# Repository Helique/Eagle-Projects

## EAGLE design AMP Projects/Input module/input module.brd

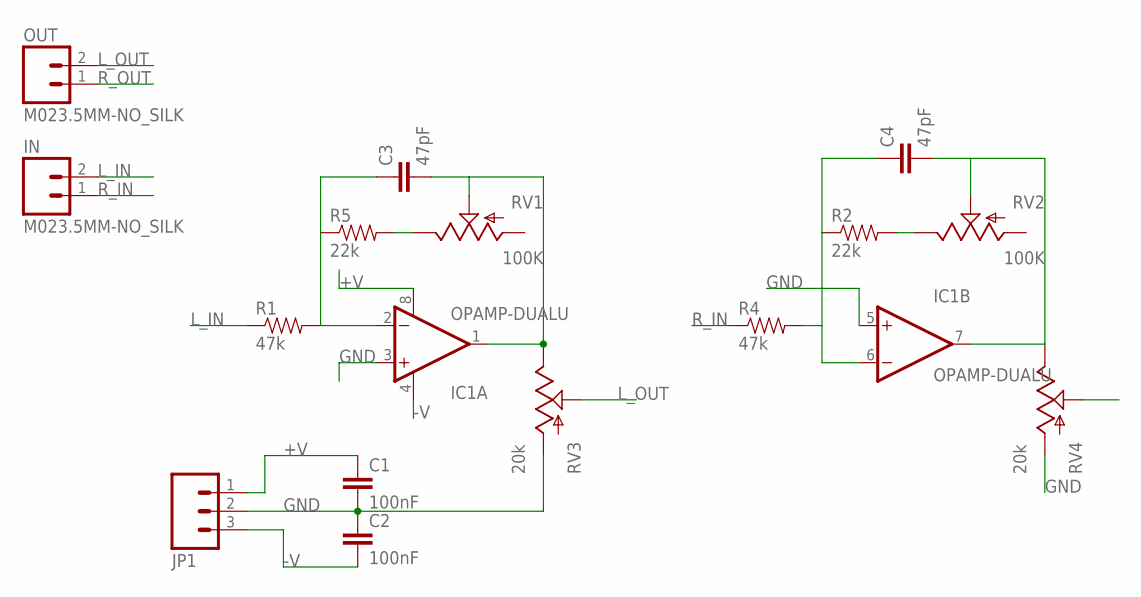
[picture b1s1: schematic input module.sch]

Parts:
C1, C2: 100nF; 1206
C3, C4: 47pF; 0805
IC1: OPAMP-DUALU; SO08
IN: M023.5MM-NO_SILK; SCREWTERMINAL-3.5MM-2-NS
JP1: M03SCREW; SCREWTERMINAL-3.5MM-3
OUT: M023.5MM-NO_SILK; SCREWTERMINAL-3.5MM-2-NS
R1, R4: 47k; AXIAL-0.4
R2, R5: 22k; AXIAL-0.4
RV1, RV2: 100K; TRIM_POT
RV3, RV4: 20k; ALPS_POT

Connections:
+V: C1.1, IC1.8 (V+), JP1.1
-V: C2.2, IC1.4 (V-), JP1.3
GND: C1.2, C2.1, IC1.3 (+IN), IC1.5 (+IN), JP1.2, RV3.P$3 (A), RV4.P$3 (A)
L_IN: IN.2, R1.P$1 (1)
L_OUT: OUT.2, RV3.P$2 (S)
unnamed: R5.P$2 (2), RV1.2 (E)
unnamed: C3.1, IC1.2 (-IN), R1.P$2 (2), R5.P$1 (1)
unnamed: C4.1, IC1.6 (-IN), R2.P$1 (1), R4.P$2 (2)
unnamed: R2.P$2 (2), RV2.2 (E)
unnamed: C4.2, IC1.7 (OUT), RV2.1 (S), RV4.P$1 (E)
unnamed: C3.2, IC1.1 (OUT), RV1.1 (S), RV3.P$1 (E)
R_IN: IN.1, R4.P$1 (1)
R_OUT: OUT.1, RV4.P$2 (S)

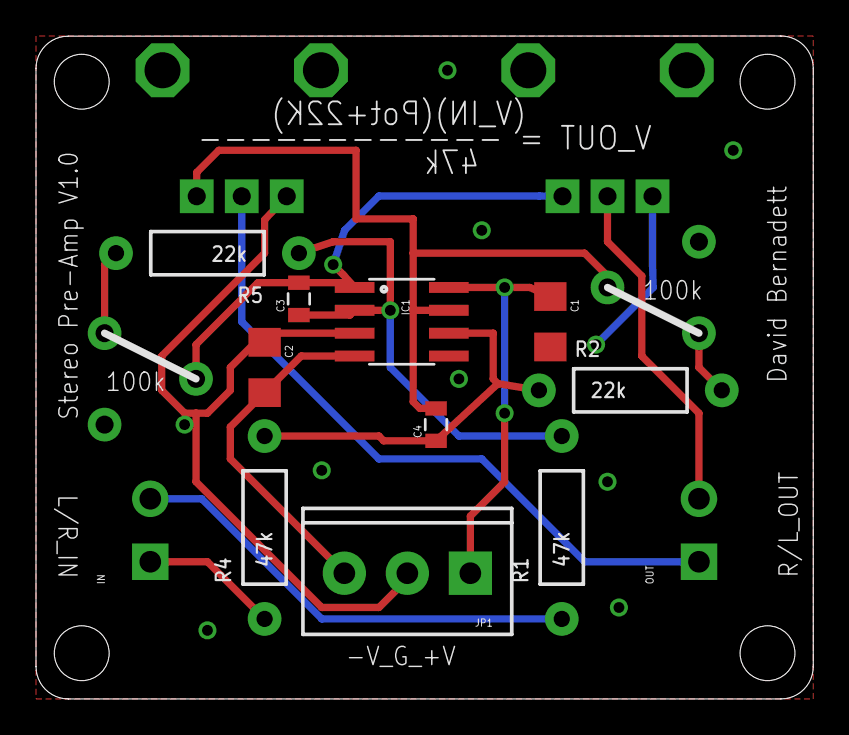
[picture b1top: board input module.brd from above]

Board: 2 copper layers, 43.2 x 36.8 mm, 20 parts (0 on the bottom side), 13 nets.

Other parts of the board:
U$1, U$2, U$3, U$4: STAND-OFF-TIGHT

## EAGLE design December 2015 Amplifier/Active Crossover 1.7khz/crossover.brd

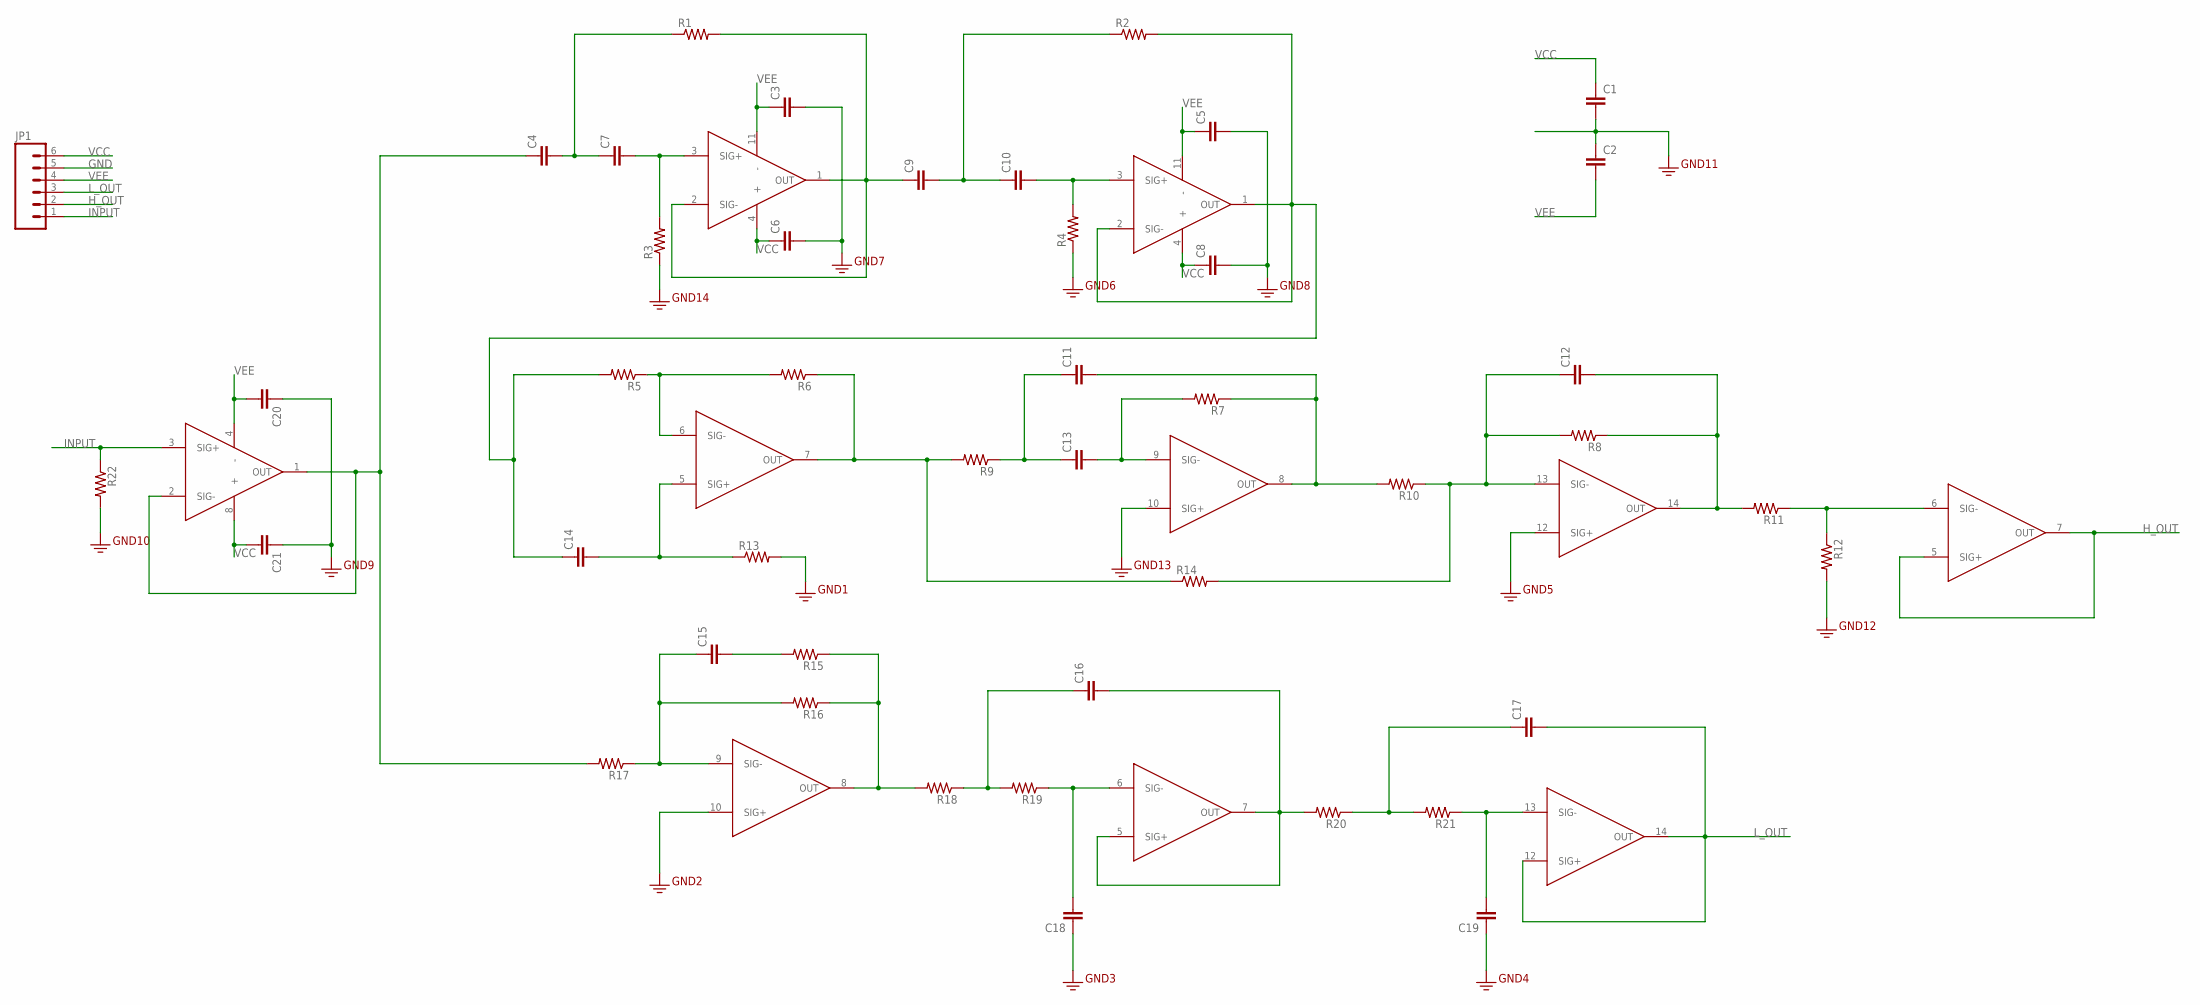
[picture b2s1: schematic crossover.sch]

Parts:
C1, C2, C3, C4, C5, C6, C7, C8, C9, C10, C11, C12, C13, C14, C15, C16, C17, C18, C19, C20, C21: CAPEZ; CAP-PTH-SMALLEZ
JP1: M06SIP; 1X06
R1, R2, R3, R4, R5, R6, R7, R8, R9, R10, R11, R12, R13, R14, R15, R16, R17, R18, R19, R20, R21, R22: RESISTORPTH-1/4W; AXIAL-0.4
U$1, U$2: OPA1604STANDARD; SOIC-14
U$3: OPA1602; SOIC8

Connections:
GND: C1.2, C2.1, C3.2, C5.2, C6.2, C8.2, C18.1, C19.1, C20.1, C21.1, JP1.5, R3.P$1 (1), R4.P$1 (1), R12.P$2 (2), R13.P$2 (2), R22.P$2 (2), U$1.10 (SIG+), U$2.10 (SIG+), U$2.12 (SIG+)
H_OUT: JP1.2, U$3.5 (SIG+), U$3.7 (OUT)
INPUT: JP1.1, R22.P$1 (1), U$3.3 (SIG+)
L_OUT: C17.2, JP1.3, U$1.12 (SIG+), U$1.14 (OUT)
unnamed: C7.2, R3.P$2 (2), U$1.3 (SIG+)
unnamed: C9.1, R1.P$2 (2), U$1.1 (OUT), U$1.2 (SIG-)
unnamed: C4.2, C7.1, R1.P$1 (1)
unnamed: C9.2, C10.1, R2.P$1 (1)
unnamed: C10.2, R4.P$2 (2), U$2.3 (SIG+)
unnamed: C11.2, R7.P$1 (1), R10.P$2 (2), U$2.8 (OUT)
unnamed: C13.2, R7.P$2 (2), U$2.9 (SIG-)
unnamed: C11.1, C13.1, R9.P$1 (1)
unnamed: R6.P$1 (1), R9.P$2 (2), R14.P$1 (1), U$2.7 (OUT)
unnamed: C14.2, R13.P$1 (1), U$2.5 (SIG+)
unnamed: C14.1, R2.P$2 (2), R5.P$2 (2), U$2.1 (OUT), U$2.2 (SIG-)
unnamed: R5.P$1 (1), R6.P$2 (2), U$2.6 (SIG-)
unnamed: C12.1, R8.P$2 (2), R10.P$1 (1), R14.P$2 (2), U$2.13 (SIG-)
unnamed: C12.2, R8.P$1 (1), R11.P$2 (2), U$2.14 (OUT)
unnamed: R11.P$1 (1), R12.P$1 (1), U$3.6 (SIG-)
unnamed: C15.1, R16.P$2 (2), R17.P$1 (1), U$1.9 (SIG-)
unnamed: C15.2, R15.P$2 (2)
unnamed: R15.P$1 (1), R16.P$1 (1), R18.P$2 (2), U$1.8 (OUT)
unnamed: C16.1, R18.P$1 (1), R19.P$2 (2)
unnamed: C18.2, R19.P$1 (1), U$1.6 (SIG-)
unnamed: C16.2, R20.P$2 (2), U$1.5 (SIG+), U$1.7 (OUT)
unnamed: C17.1, R20.P$1 (1), R21.P$2 (2)
unnamed: C19.2, R21.P$1 (1), U$1.13 (SIG-)
unnamed: C4.1, R17.P$2 (2), U$3.1 (OUT), U$3.2 (SIG-)
VCC: C1.1, C6.1, C8.1, C21.2, JP1.6, U$1.4 (+), U$2.4 (+), U$3.8 (+)
VEE: C2.2, C3.1, C5.1, C20.2, JP1.4, U$1.11 (-), U$2.11 (-), U$3.4 (-)

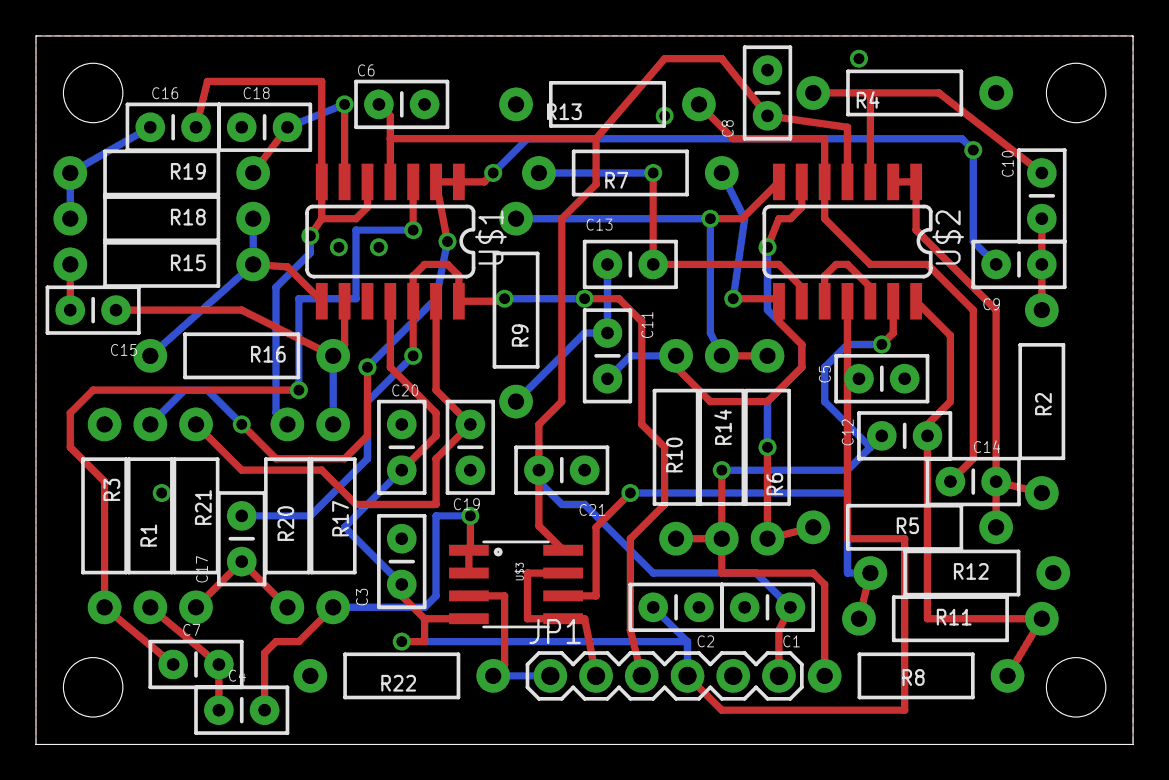
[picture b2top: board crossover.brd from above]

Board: 2 copper layers, 60.9 x 39.4 mm, 51 parts (0 on the bottom side), 30 nets.

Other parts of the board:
U$4, U$5, U$6, U$7: STAND-OFF

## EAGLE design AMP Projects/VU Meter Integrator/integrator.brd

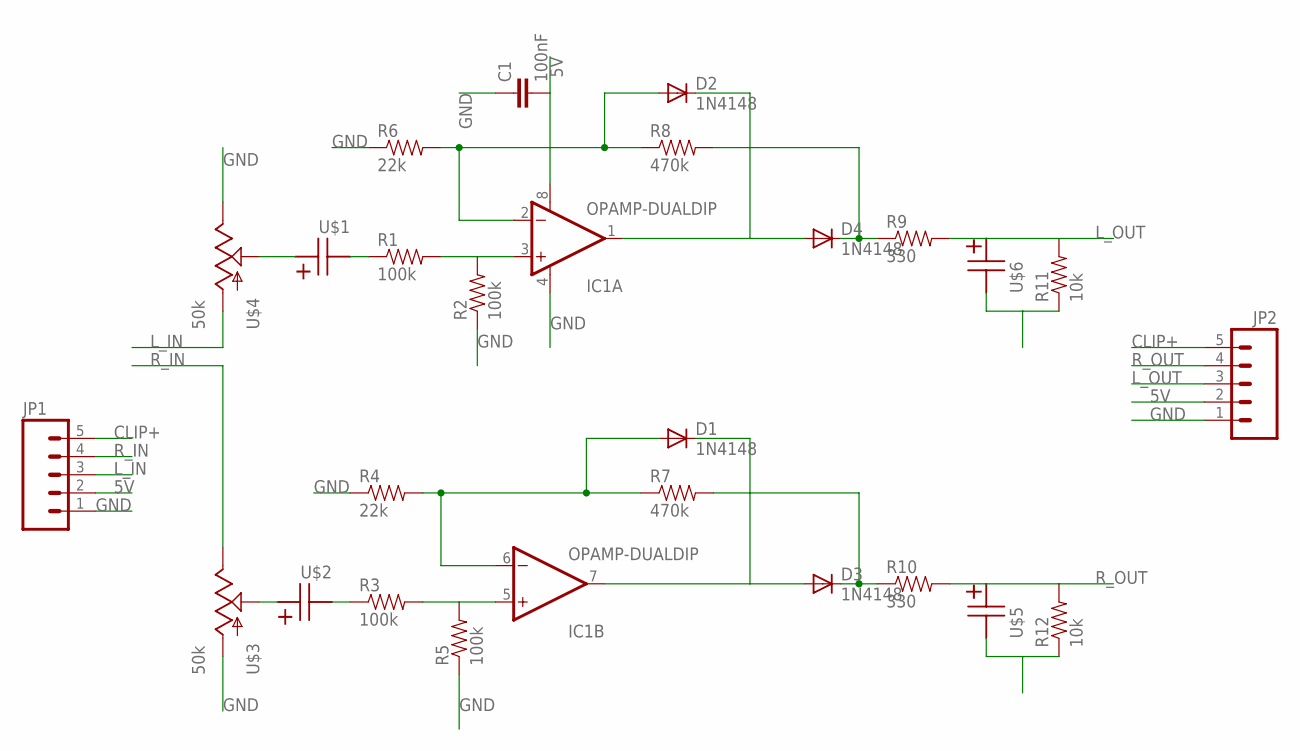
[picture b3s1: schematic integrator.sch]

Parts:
C1: 100nF; 1206
D1, D2, D3, D4: 1N4148; DIODE-1N4148
IC1: OPAMP-DUALDIP; DIP08
JP1, JP2: M05SMD2; 1X05-1MM-RA
R1, R2, R3, R5: 100k; AXIAL-0.4
R4, R6: 22k; AXIAL-0.4
R7, R8: 470k; AXIAL-0.4
R9, R10: 330; AXIAL-0.4
R11, R12: 10k; AXIAL-0.4
U$1, U$2: 6.8uF; 2MMLEAD_5MMDIAMETER
U$3, U$4: 50k; ALPS_POT
U$5, U$6: 2.2uF; 2MMLEAD_5MMDIAMETER

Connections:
5V: C1.2, IC1.8 (V+), JP1.2, JP2.2
CLIP+: JP1.5, JP2.5
GND: C1.1, IC1.4 (V-), JP1.1, JP2.1, R2.P$1 (1), R4.P$1 (1), R5.P$1 (1), R6.P$1 (1), R11.P$1 (1), R12.P$1 (1), U$3.P$3 (A), U$4.P$1 (E), U$5.-, U$6.-
L_IN: JP1.3, U$4.P$3 (A)
L_OUT: JP2.3, R9.P$2 (2), R11.P$2 (2), U$6.+
unnamed: D1.A, IC1.6 (-IN), R4.P$2 (2), R7.P$1 (1)
unnamed: D2.A, IC1.2 (-IN), R6.P$2 (2), R8.P$1 (1)
unnamed: IC1.5 (+IN), R3.P$2 (2), R5.P$2 (2)
unnamed: IC1.3 (+IN), R1.P$2 (2), R2.P$2 (2)
unnamed: D1.C, D3.A, IC1.7 (OUT)
unnamed: D3.C, R7.P$2 (2), R10.P$1 (1)
unnamed: D4.C, R8.P$2 (2), R9.P$1 (1)
unnamed: D2.C, D4.A, IC1.1 (OUT)
unnamed: U$2.+, U$3.P$2 (S)
unnamed: R1.P$1 (1), U$1.-
unnamed: R3.P$1 (1), U$2.-
unnamed: U$1.+, U$4.P$2 (S)
R_IN: JP1.4, U$3.P$1 (E)
R_OUT: JP2.4, R10.P$2 (2), R12.P$2 (2), U$5.+

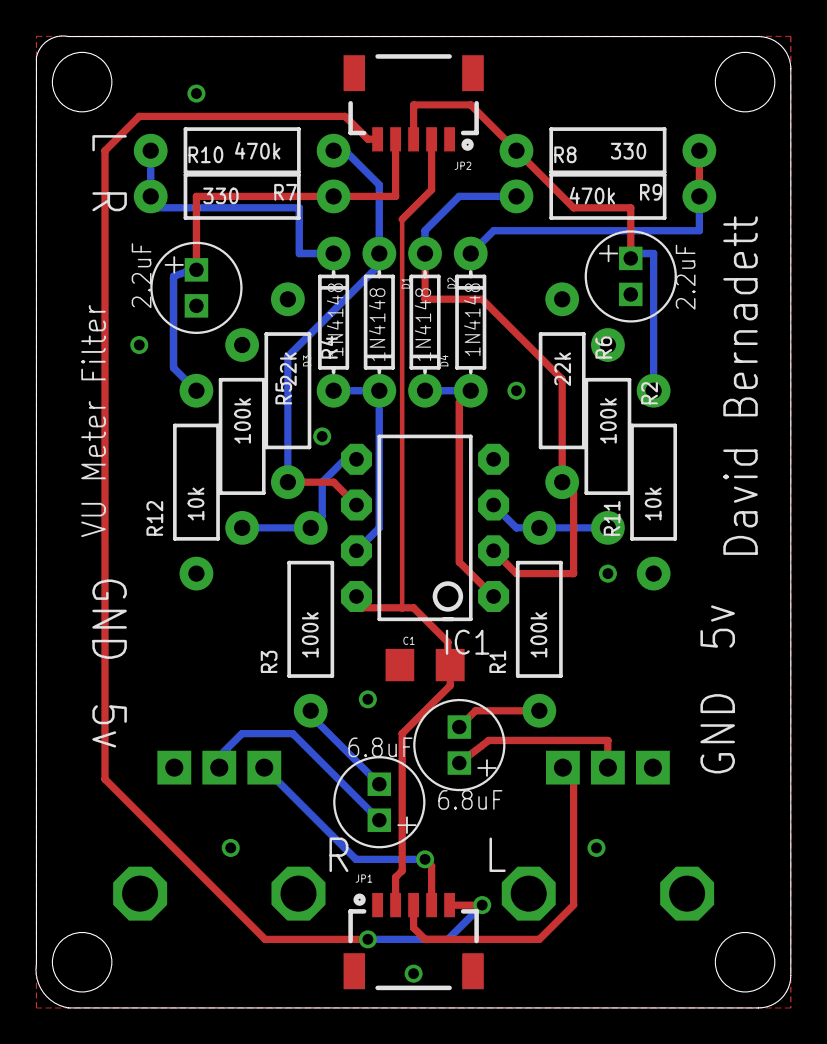
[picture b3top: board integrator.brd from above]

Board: 2 copper layers, 41.9 x 54.0 mm, 30 parts (0 on the bottom side), 19 nets.

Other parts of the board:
U$7, U$8, U$9, U$10: STAND-OFF

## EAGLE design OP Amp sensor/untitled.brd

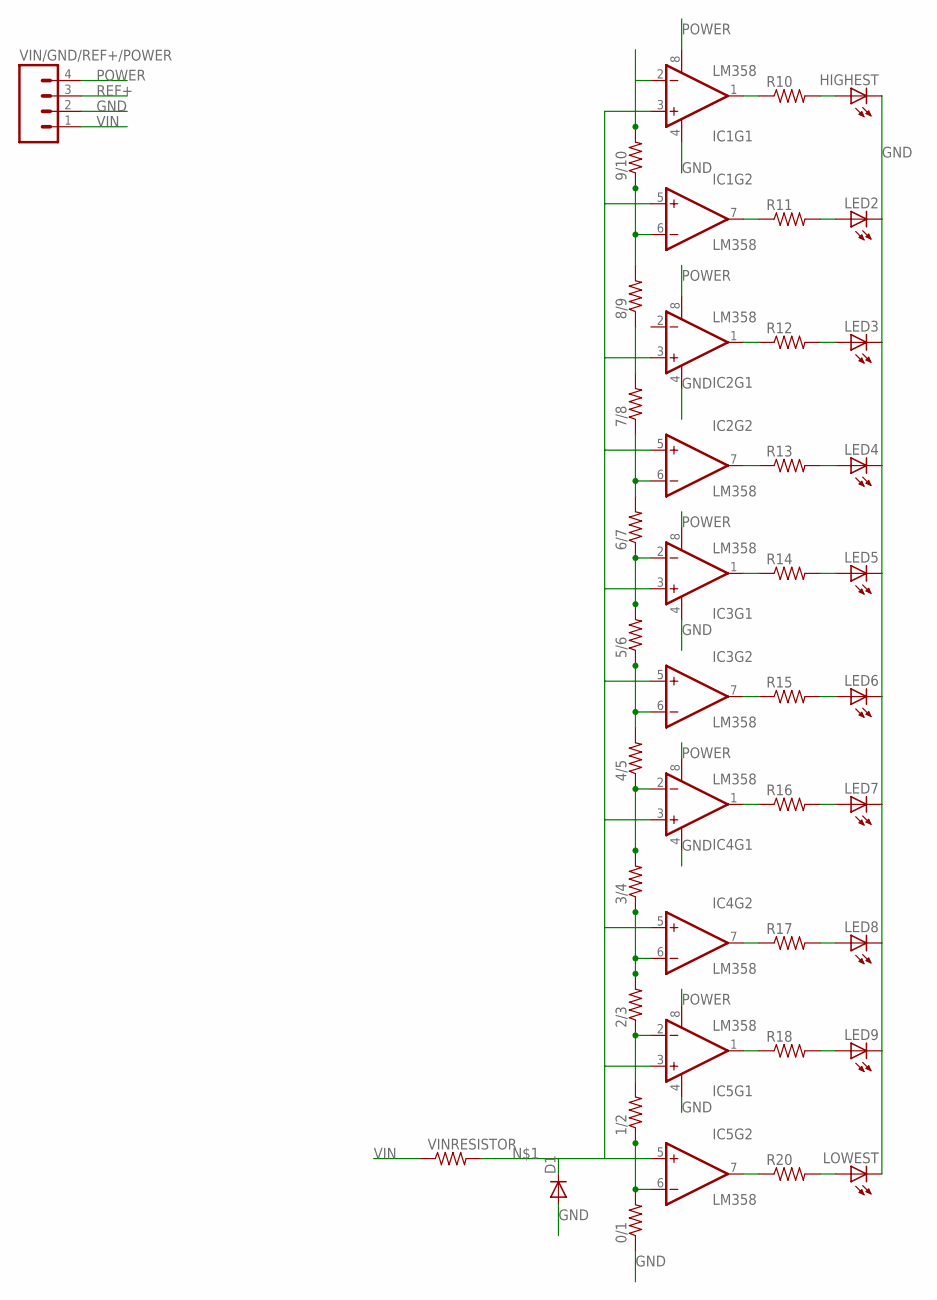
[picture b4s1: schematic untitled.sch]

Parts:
0/1, 1/2, 2/3, 3/4, 4/5, 5/6, 6/7, 7/8, 8/9, 9/10: RESISTORPTH-1/4W; AXIAL-0.4
D1: DIODE1N4148; DIODE-1N4148
HIGHEST: LED5MM
IC1, IC2, IC3, IC4, IC5: LM358; DIP08
LED2, LED3, LED4, LED5, LED6, LED7, LED8, LED9: LED5MM
LOWEST: LED5MM
R10, R11, R12, R13, R14, R15, R16, R17, R18, R20: RESISTORPTH-1/4W; AXIAL-0.4
VIN/GND/REF+/POWER: M04PTH; 1X04
VINRESISTOR: RESISTORPTH-1/4W; AXIAL-0.4

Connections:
GND: 0/1.P$1 (1), D1.A, HIGHEST.K (C), IC1.4 (V-), IC2.4 (V-), IC3.4 (V-), IC4.4 (V-), IC5.4 (V-), LED2.K (C), LED3.K (C), LED4.K (C), LED5.K (C), LED6.K (C), LED7.K (C), LED8.K (C), LED9.K (C), LOWEST.K (C), VIN/GND/REF+/POWER.2
unnamed: D1.C, IC1.3 (+IN), IC1.5 (+IN), IC2.3 (+IN), IC2.5 (+IN), IC3.3 (+IN), IC3.5 (+IN), IC4.3 (+IN), IC4.5 (+IN), IC5.3 (+IN), IC5.5 (+IN), VINRESISTOR.P$2 (2)
unnamed: 8/9.P$2 (2), 9/10.P$1 (1), IC1.6 (-IN)
unnamed: 7/8.P$2 (2), 8/9.P$1 (1)
unnamed: 6/7.P$2 (2), 7/8.P$1 (1), IC2.6 (-IN)
unnamed: 5/6.P$2 (2), 6/7.P$1 (1), IC3.2 (-IN)
unnamed: 4/5.P$2 (2), 5/6.P$1 (1), IC3.6 (-IN)
unnamed: 3/4.P$2 (2), 4/5.P$1 (1), IC4.2 (-IN)
unnamed: 2/3.P$2 (2), 3/4.P$1 (1), IC4.6 (-IN)
unnamed: 1/2.P$2 (2), 2/3.P$1 (1), IC5.2 (-IN)
unnamed: 0/1.P$2 (2), 1/2.P$1 (1), IC5.6 (-IN)
unnamed: IC5.7 (OUT), R20.P$1 (1)
unnamed: IC5.1 (OUT), R18.P$1 (1)
unnamed: IC4.7 (OUT), R17.P$1 (1)
unnamed: IC4.1 (OUT), R16.P$1 (1)
unnamed: IC3.7 (OUT), R15.P$1 (1)
unnamed: IC3.1 (OUT), R14.P$1 (1)
unnamed: IC2.7 (OUT), R13.P$1 (1)
unnamed: IC2.1 (OUT), R12.P$1 (1)
unnamed: IC1.7 (OUT), R11.P$1 (1)
unnamed: IC1.1 (OUT), R10.P$1 (1)
unnamed: HIGHEST.A, R10.P$2 (2)
unnamed: LED2.A, R11.P$2 (2)
unnamed: LED3.A, R12.P$2 (2)
unnamed: LED4.A, R13.P$2 (2)
unnamed: LED5.A, R14.P$2 (2)
unnamed: LED6.A, R15.P$2 (2)
unnamed: LED7.A, R16.P$2 (2)
unnamed: LED8.A, R17.P$2 (2)
unnamed: LED9.A, R18.P$2 (2)
unnamed: LOWEST.A, R20.P$2 (2)
POWER: IC1.8 (V+), IC2.8 (V+), IC3.8 (V+), IC4.8 (V+), IC5.8 (V+), VIN/GND/REF+/POWER.4
REF+: 9/10.P$2 (2), IC1.2 (-IN), VIN/GND/REF+/POWER.3
VIN: VIN/GND/REF+/POWER.1, VINRESISTOR.P$1 (1)

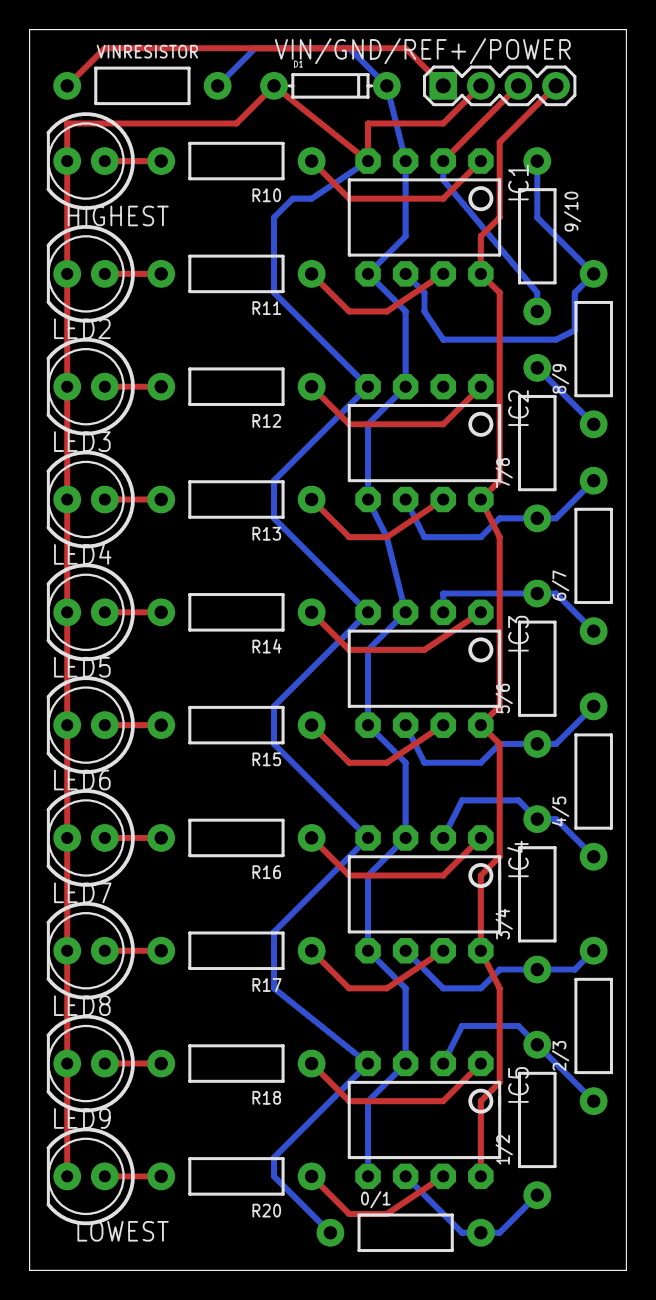
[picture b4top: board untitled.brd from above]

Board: 2 copper layers, 40.3 x 83.8 mm, 38 parts (0 on the bottom side), 34 nets.

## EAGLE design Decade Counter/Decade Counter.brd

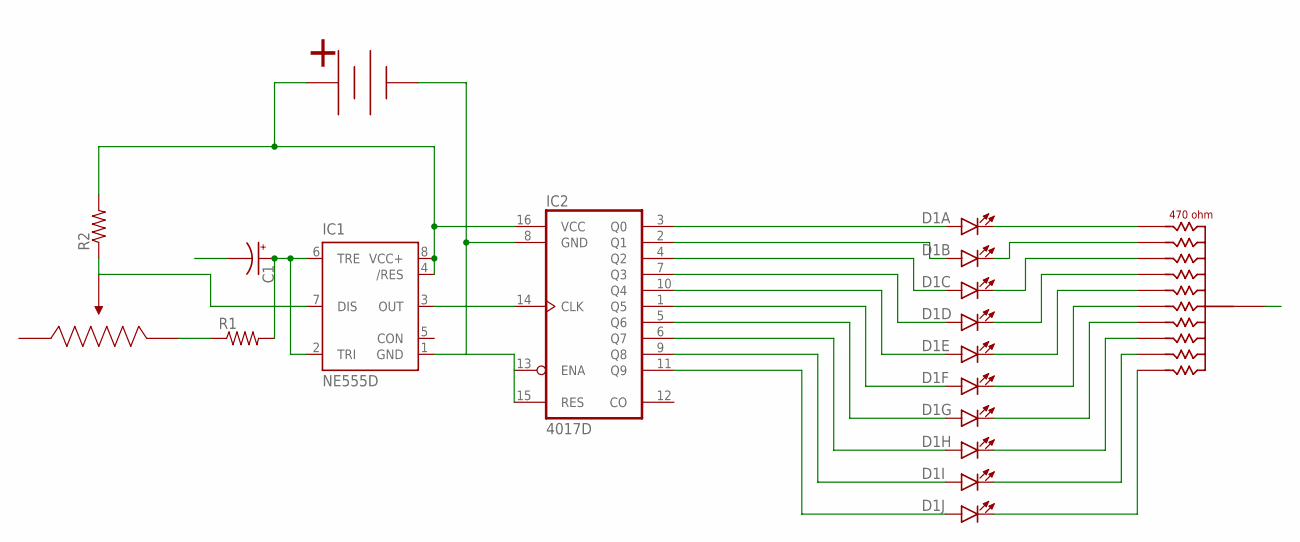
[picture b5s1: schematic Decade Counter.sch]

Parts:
470OHM: 470 ohm; 11-PIN-RESISTOR
C1: CAP_POLPTH1; CPOL-RADIAL-100UF-25V
D1: LED_BARGRAPH_10; LED_BARGAPH_10
IC1: NE555D; SO08
IC2: 4017D; SO16
R1, R2: RESISTOR0805-RES; 0805
U$1: VERTICAL_TRIM_POT; TRIM-POT-VERTICLE
U$2: COIN-BATTERY-12MM-BOTTOM; BATTCON_12MM_BOTTOM

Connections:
GND: 470OHM.COMMON, C1.2 (-), IC1.1 (GND), IC2.8 (GND), IC2.13 (ENA), IC2.15 (RES), U$2.GND
unnamed: 470OHM.1, D1.20 (C)
unnamed: 470OHM.2, D1.19 (C)
unnamed: 470OHM.3, D1.18 (C)
unnamed: 470OHM.4, D1.17 (C)
unnamed: 470OHM.5, D1.16 (C)
unnamed: 470OHM.6, D1.15 (C)
unnamed: 470OHM.7, D1.14 (C)
unnamed: 470OHM.8, D1.13 (C)
unnamed: 470OHM.9, D1.12 (C)
unnamed: 470OHM.10, D1.11 (C)
unnamed: D1.1 (A), IC2.3 (Q0)
unnamed: D1.2 (A), IC2.2 (Q1)
unnamed: D1.3 (A), IC2.4 (Q2)
unnamed: D1.4 (A), IC2.7 (Q3)
unnamed: D1.5 (A), IC2.10 (Q4)
unnamed: D1.6 (A), IC2.1 (Q5)
unnamed: D1.7 (A), IC2.5 (Q6)
unnamed: D1.8 (A), IC2.6 (Q7)
unnamed: D1.9 (A), IC2.9 (Q8)
unnamed: D1.10 (A), IC2.11 (Q9)
unnamed: IC1.3 (OUT), IC2.14 (CLK)
unnamed: R1.1, U$1.3
unnamed: IC1.7 (DIS), R2.1, U$1.WIPER2 (WIPER)
unnamed: C1.1 (+), IC1.2 (TRI), IC1.6 (TRE), R1.2
VCC: IC1.4 (/RES), IC1.8 (VCC+), IC2.16 (VCC), R2.2, U$2.PWR@1 (PWR), U$2.PWR@2 (PWR)

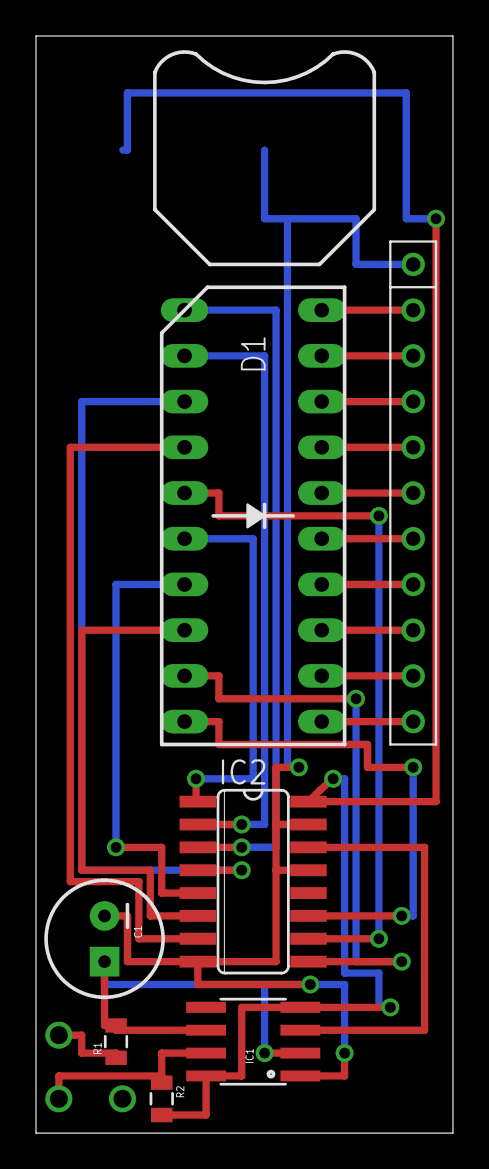
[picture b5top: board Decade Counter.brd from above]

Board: 2 copper layers, 23.2 x 61.0 mm, 9 parts (0 on the bottom side), 26 nets.

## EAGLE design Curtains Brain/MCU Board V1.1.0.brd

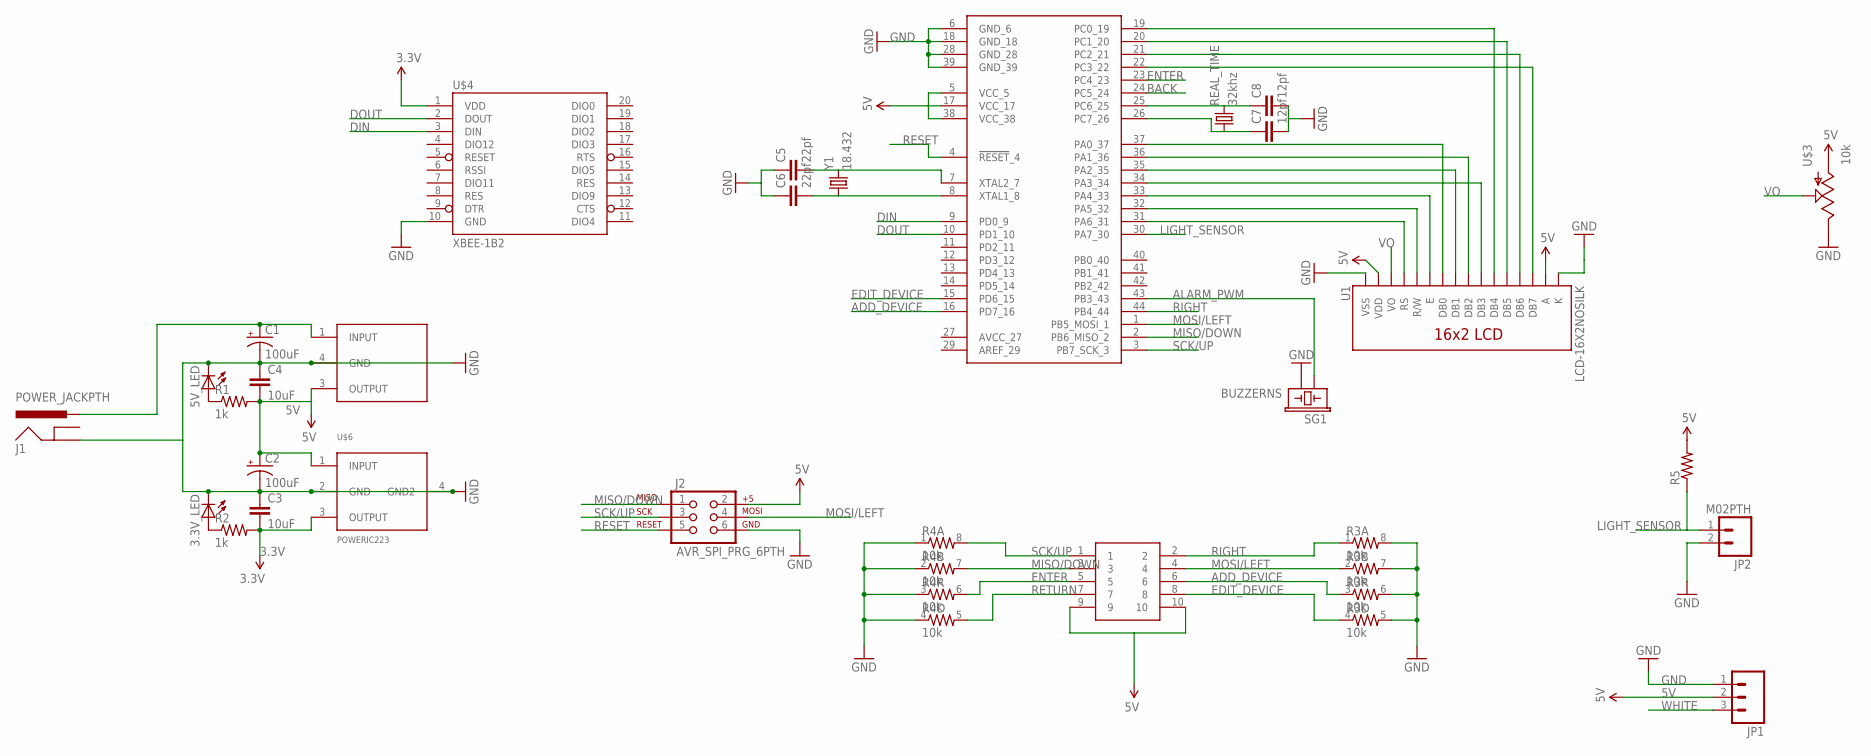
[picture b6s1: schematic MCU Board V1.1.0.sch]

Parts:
3.3V_LED, 5V_LED: LED1206; LED-1206
C1, C2: 100uF; PANASONIC_D
C3, C4: 10uF; 1206
C5, C6: 22pf; 0805
C7, C8: 12pf; 0805
J1: POWER_JACKPTH; POWER_JACK_PTH
J2: AVR_SPI_PRG_6PTH; 2X3
JP1: M03PTH; 1X03
JP2: M02PTH; 1X02
R1, R2: 1k; 1206
R3, R4: 10k; 0603-ARV
R5: RESISTOR1206; 1206
REAL_TIME: 32khz; TC26H
SG1: BUZZERNS; BUZZER-12MM-NS
U1: LCD-16X2NOSILK; LCD-16X2_NOSILK
U$1: ATMEGA1284; TQFP44
U$2: 10PIN_HEADER_MALETHROUGH-HOLE; 2X5-SHROUDED
U$3: 10k; TRIM_POT
U$4: XBEE-1B2; XBEE-SILK
U$5: DPACK_V_REG; DPAK
U$6: POWERIC223; SOT223
Y1: 18.432; HC49US

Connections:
3.3V: C3.2, R2.2, U$4.1 (VDD), U$6.3 (OUTPUT)
5V: C2.+, C4.2, J2.2, JP1.2, R1.2, R5.2, U1.2 (VDD), U1.15 (A), U$1.5 (VCC_5), U$1.17 (VCC_17), U$1.38 (VCC_38), U$2.9, U$2.10, U$3.3 (A), U$5.3 (OUTPUT), U$6.1 (INPUT)
ADD_DEVICE: R3.3 (1), U$1.16 (PD7_16), U$2.6
ALARM_PWM: SG1.+ (1), U$1.43 (PB3_43)
BACK: U$1.24 (PC5_24)
DIN: U$1.9 (PD0_9), U$4.3 (DIN)
DOUT: U$1.10 (PD1_10), U$4.2 (DOUT)
EDIT_DEVICE: R3.4 (1), U$1.15 (PD6_15), U$2.8
ENTER: R4.6 (2), U$1.23 (PC4_23), U$2.5
GND: 3.3V_LED.C, 5V_LED.C, C1.-, C2.-, C3.1, C4.1, C5.1, C6.1, C7.2, C8.2, J1.GND, J2.6, JP1.1, JP2.2, R3.5 (2), R3.6 (2), R3.7 (2), R3.8 (2), R4.1, R4.2 (1), R4.3 (1), R4.4 (1), SG1.- (2), U1.1 (VSS), U1.16 (K), U$1.6 (GND_6), U$1.18 (GND_18), U$1.28 (GND_28), U$1.39 (GND_39), U$3.2 (E), U$4.10 (GND), U$5.4 (GND), U$6.2 (GND), U$6.4 (GND2)
LIGHT_SENSOR: JP2.1, R5.1, U$1.30 (PA7_30)
MISO/DOWN: J2.1, R4.7 (2), U$1.2 (PB6_MISO_2), U$2.3
MOSI/LEFT: J2.4, R3.2 (1), U$1.1 (PB5_MOSI_1), U$2.4
unnamed: C7.1, REAL_TIME.1, U$1.26 (PC7_26)
unnamed: C5.2, U$1.7 (XTAL2_7), Y1.2
unnamed: C6.2, U$1.8 (XTAL1_8), Y1.1
unnamed: C8.1, REAL_TIME.2, U$1.25 (PC6_25)
unnamed: 5V_LED.A, R1.1
unnamed: 3.3V_LED.A, R2.1
unnamed: U1.7 (DB0), U$1.37 (PA0_37)
unnamed: U1.9 (DB2), U$1.36 (PA1_36)
unnamed: U1.8 (DB1), U$1.35 (PA2_35)
unnamed: U1.10 (DB3), U$1.34 (PA3_34)
unnamed: U1.6 (E), U$1.33 (PA4_33)
unnamed: U1.5 (R/W), U$1.32 (PA5_32)
unnamed: U1.4 (RS), U$1.31 (PA6_31)
unnamed: U1.11 (DB4), U$1.19 (PC0_19)
unnamed: U1.12 (DB5), U$1.20 (PC1_20)
unnamed: U1.13 (DB6), U$1.21 (PC2_21)
unnamed: U1.14 (DB7), U$1.22 (PC3_22)
PWR: C1.+, J1.PWR, U$5.1 (INPUT)
RESET: J2.5, U$1.4 (!RESET!_4)
RETURN: R4.5 (2), U$2.7
RIGHT: R3.1, U$1.44 (PB4_44), U$2.2
SCK/UP: J2.3, R4.8 (2), U$1.3 (PB7_SCK_3), U$2.1
VO: U1.3 (VO), U$3.1 (S)
WHITE: JP1.3

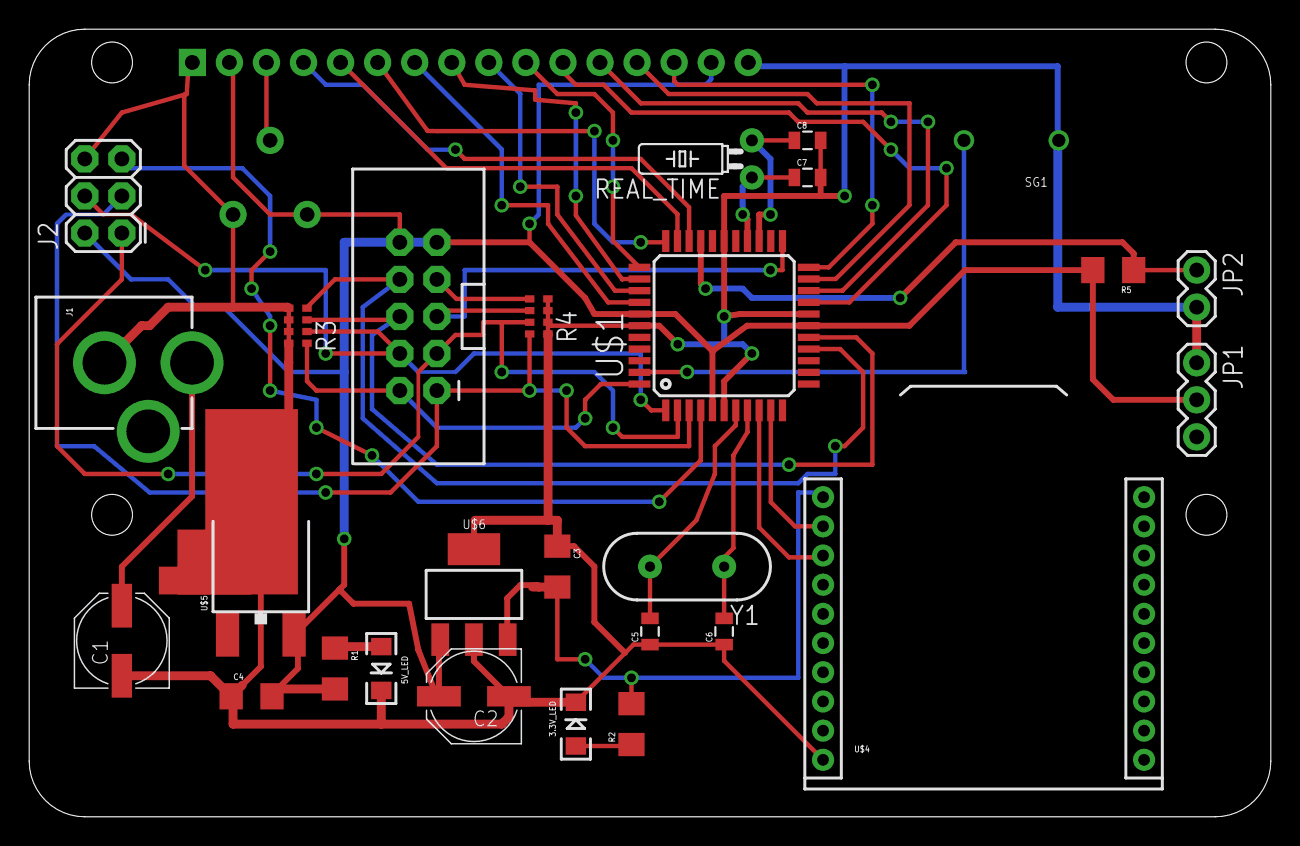
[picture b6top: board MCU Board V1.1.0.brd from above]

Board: 2 copper layers, 85.1 x 54.0 mm, 29 parts (0 on the bottom side), 35 nets.

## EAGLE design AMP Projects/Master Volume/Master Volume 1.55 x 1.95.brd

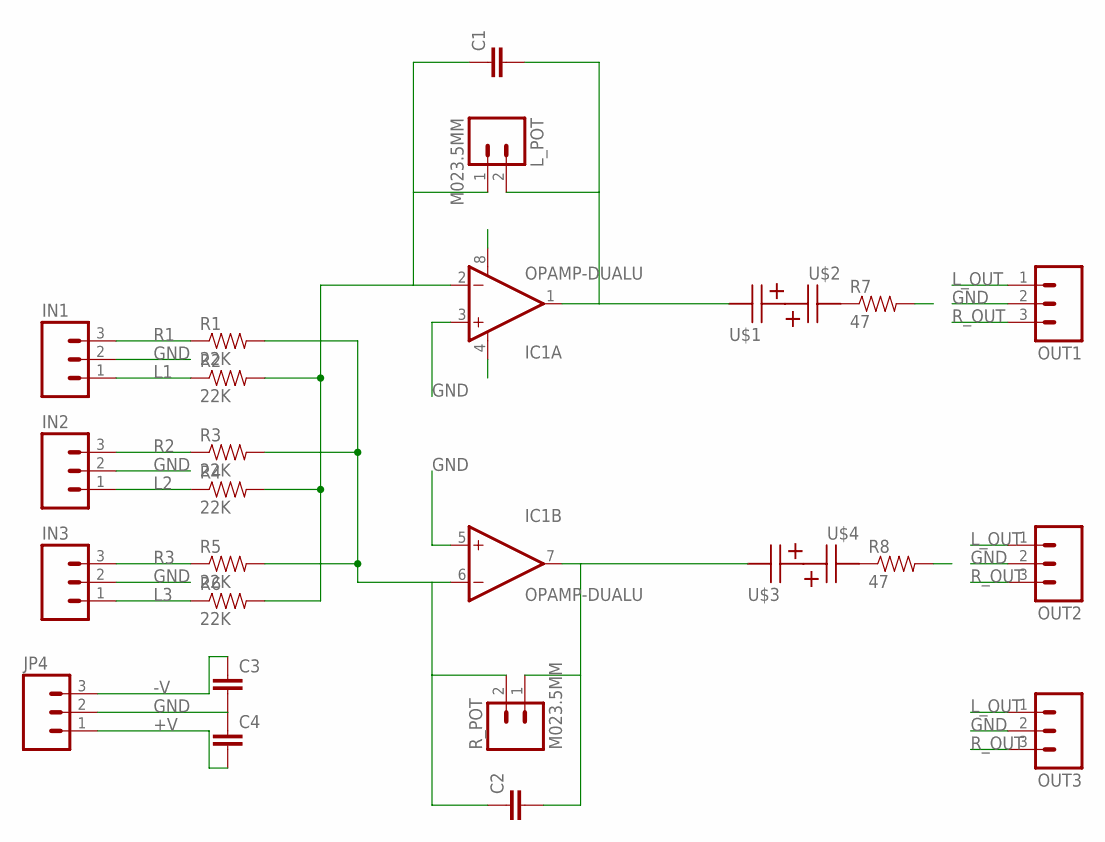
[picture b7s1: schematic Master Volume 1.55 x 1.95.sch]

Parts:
C1, C2: CAP0805; 0805
C3, C4: CAP1206; 1206
IC1: OPAMP-DUALU; SO08
IN1, IN2, IN3: M03SCREW; SCREWTERMINAL-3.5MM-3
JP4: M03SCREW; SCREWTERMINAL-3.5MM-3
L_POT: M023.5MM; SCREWTERMINAL-3.5MM-2
OUT1, OUT2, OUT3: M03SCREW; SCREWTERMINAL-3.5MM-3
R1, R2, R3, R4, R5, R6: 22K; AXIAL-0.4
R7, R8: 47; AXIAL-0.4
R_POT: M023.5MM; SCREWTERMINAL-3.5MM-2
U$1, U$2, U$3, U$4: 5MM-12.5MM-POLAR2MMX5MM; 2MMLEAD_5MMDIAMETER

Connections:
+V: C4.2, IC1.8 (V+), JP4.1
-V: C3.1, IC1.4 (V-), JP4.3
GND: C3.2, C4.1, IC1.3 (+IN), IC1.5 (+IN), IN1.2, IN2.2, IN3.2, JP4.2, OUT1.2, OUT2.2, OUT3.2
L1: IN1.1, R2.P$1 (1)
L2: IN2.1, R4.P$1 (1)
L3: IN3.1, R6.P$1 (1)
L_OUT: OUT1.1, OUT2.1, OUT3.1, R7.P$2 (2)
unnamed: C1.1, IC1.2 (-IN), L_POT.1, R2.P$2 (2), R4.P$2 (2), R6.P$2 (2)
unnamed: C2.1, IC1.6 (-IN), R1.P$2 (2), R3.P$2 (2), R5.P$2 (2), R_POT.2
unnamed: C1.2, IC1.1 (OUT), L_POT.2, U$1.+ (-)
unnamed: C2.2, IC1.7 (OUT), R_POT.1, U$3.+ (-)
unnamed: U$1.- (+), U$2.- (+)
unnamed: U$3.- (+), U$4.- (+)
unnamed: R7.P$1 (1), U$2.+ (-)
unnamed: R8.P$1 (1), U$4.+ (-)
R1: IN1.3, R1.P$1 (1)
R2: IN2.3, R3.P$1 (1)
R3: IN3.3, R5.P$1 (1)
R_OUT: OUT1.3, OUT2.3, OUT3.3, R8.P$2 (2)

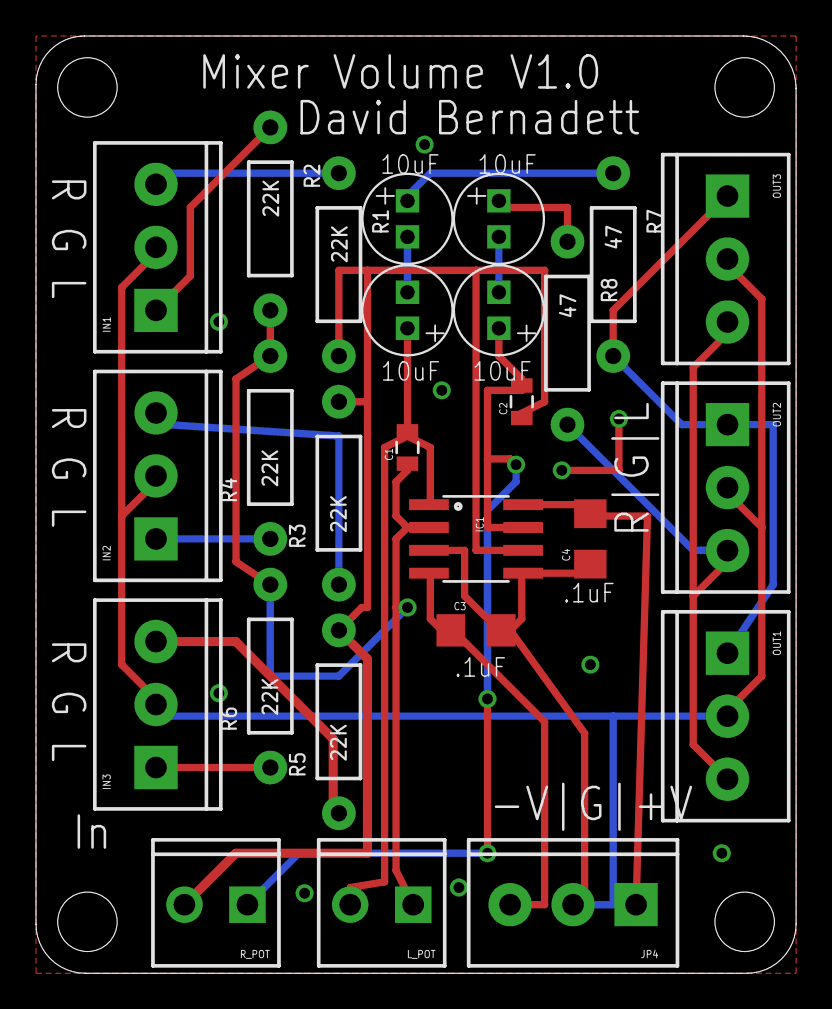
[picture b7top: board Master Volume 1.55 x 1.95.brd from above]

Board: 2 copper layers, 42.2 x 52.1 mm, 30 parts (0 on the bottom side), 19 nets.

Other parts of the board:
U$5, U$6, U$7, U$8: STAND-OFF

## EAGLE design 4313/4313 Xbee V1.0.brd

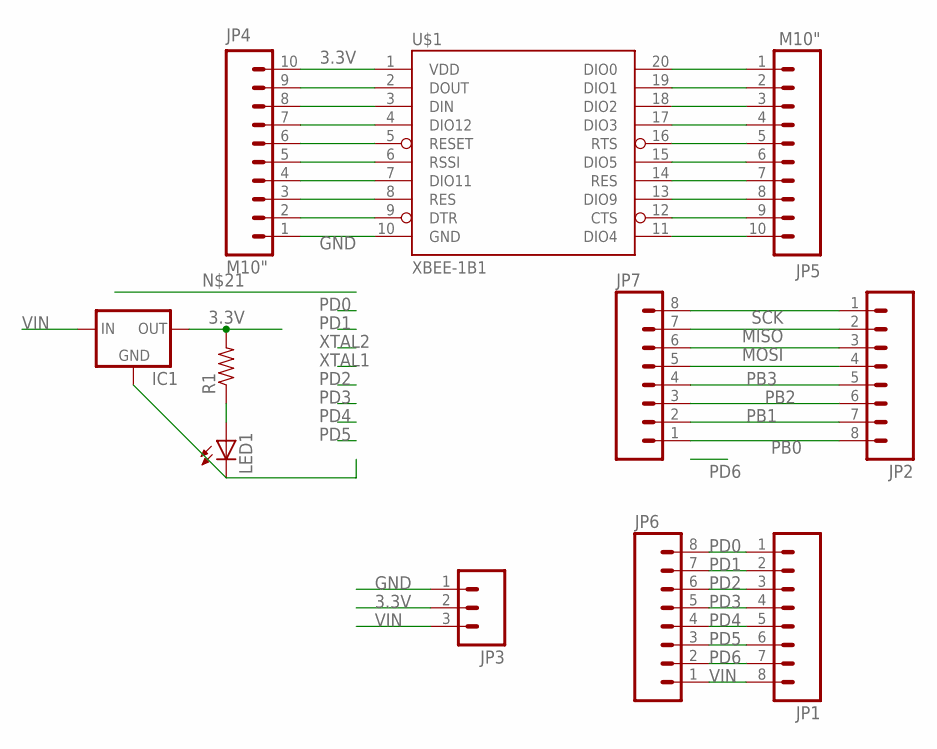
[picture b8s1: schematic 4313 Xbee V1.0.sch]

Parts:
IC1: V_REG_78XXSIDE; 78XXL
JP1, JP2, JP6, JP7: M081X08; 1X08
JP3: M03PTH; 1X03
JP4, JP5: M10"; 1X10
LED1: LED1206; LED-1206
R1: RESISTOR1206; 1206
U$1: XBEE-1B1; XBEE-1

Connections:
3.3V: IC1.OUT, JP3.2, JP4.10, R1.2, U$1.1 (VDD)
GND: IC1.GND, JP3.1, JP4.1, LED1.C, U$1.10 (GND)
MISO: JP2.2, JP7.7
MOSI: JP2.3, JP7.6
unnamed: LED1.A, R1.1
unnamed: JP4.2, U$1.9 (DTR)
unnamed: JP4.3, U$1.8 (RES)
unnamed: JP4.4, U$1.7 (DIO11)
unnamed: JP4.5, U$1.6 (RSSI)
unnamed: JP4.6, U$1.5 (RESET)
unnamed: JP4.7, U$1.4 (DIO12)
unnamed: JP4.8, U$1.3 (DIN)
unnamed: JP4.9, U$1.2 (DOUT)
unnamed: JP5.1, U$1.20 (DIO0)
unnamed: JP5.2, U$1.19 (DIO1)
unnamed: JP5.3, U$1.18 (DIO2)
unnamed: JP5.4, U$1.17 (DIO3)
unnamed: JP5.5, U$1.16 (RTS)
unnamed: JP5.6, U$1.15 (DIO5)
unnamed: JP5.7, U$1.14 (RES)
unnamed: JP5.8, U$1.13 (DIO9)
unnamed: JP5.9, U$1.12 (CTS)
unnamed: JP5.10, U$1.11 (DIO4)
PB0: JP2.8, JP7.1
PB1: JP2.7, JP7.2
PB2: JP2.6, JP7.3
PB3: JP2.5, JP7.4
PB4: JP2.4, JP7.5
PD0: JP1.1, JP6.8
PD1: JP1.2, JP6.7
PD2: JP1.3, JP6.6
PD3: JP1.4, JP6.5
PD4: JP1.5, JP6.4
PD5: JP1.6, JP6.3
PD6: JP1.7, JP6.2
SCK: JP2.1, JP7.8
VIN: IC1.IN, JP1.8, JP3.3, JP6.1

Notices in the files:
parts and their libraries:
SparkFun-PowerIC: Licensing: CC v3.0 Share-Alike You are welcome to use this library for commercial purposes.
